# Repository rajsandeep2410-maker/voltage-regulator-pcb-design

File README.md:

# 🔌 Voltage Regulator PCB Design using KiCad

## 📌 Overview

This project involves the design and development of a voltage regulator circuit and its PCB layout using KiCad. The objective was to create a stable voltage output circuit and implement it on a printed circuit board.

---

## ⚙️ Design Process

* Created circuit schematic using KiCad
* Selected appropriate electronic components
* Designed PCB layout and routing
* Ensured proper connections and basic layout practices

---

## 🔧 Tools Used

* KiCad (Schematic and PCB Design)

---

## 🚀 Key Concepts

* PCB Design Workflow
* Schematic Capture
* Component Selection
* PCB Routing Basics

---

## 👨‍💻 Author

Sandeep Raj

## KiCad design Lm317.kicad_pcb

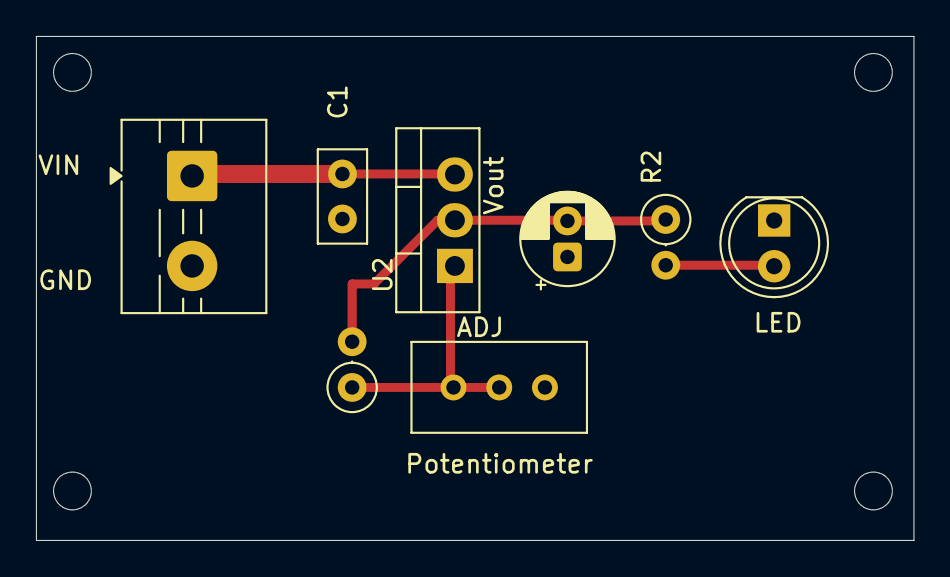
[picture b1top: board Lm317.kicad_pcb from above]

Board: 2 copper layers, 48.8 x 28.0 mm, 8 parts (0 on the bottom side), 5 nets.

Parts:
C1: 0.1u; C_Disc_D5.0mm_W2.5mm_P2.50mm
C2: 10u; CP_Radial_D5.0mm_P2.00mm
D1: LED; LED_D5.0mm
J1: Conn_01x02; TerminalBlock_MaiXu_MX126-5.0-02P_1x02_P5.00mm
Potentiometer: 5k; Potentiometer_Bourns_3296W_Vertical
R1: 240; R_Axial_DIN0207_L6.3mm_D2.5mm_P2.54mm_Vertical
R2: 330; R_Axial_DIN0207_L6.3mm_D2.5mm_P2.54mm_Vertical
U2: LM317_TO-220; TO-220-3_Vertical

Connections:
+5V: C1.1, J1.1, U2.3 (VI)
GND: C1.2, C2.1, D1.1 (K), J1.2, Potentiometer.3
unnamed: D1.2 (A), R2.2
unnamed: Potentiometer.1, Potentiometer.2, R1.1, U2.1 (ADJ)
unnamed: C2.2, R1.2, R2.1, U2.2 (VO)

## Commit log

2026-04-03 Revise README for voltage regulator PCB design project
    Updated README to enhance project description and structure.
